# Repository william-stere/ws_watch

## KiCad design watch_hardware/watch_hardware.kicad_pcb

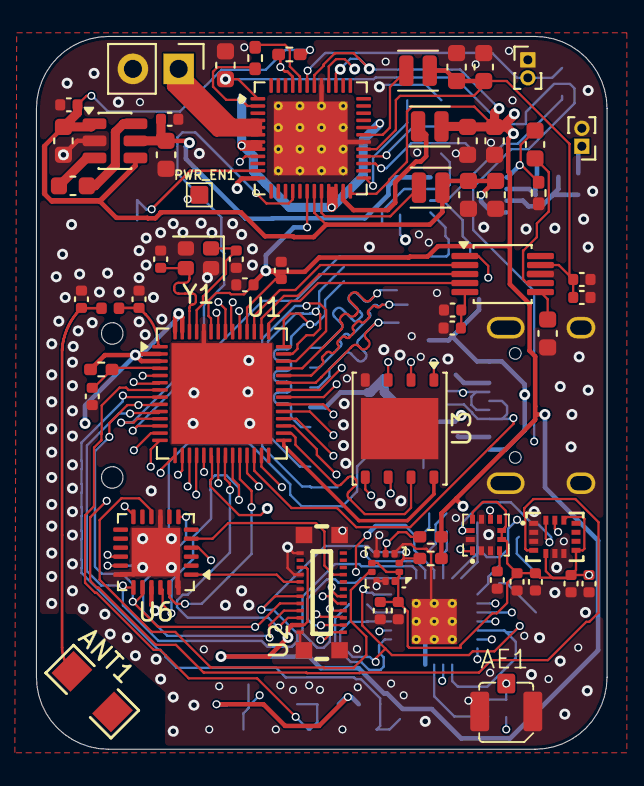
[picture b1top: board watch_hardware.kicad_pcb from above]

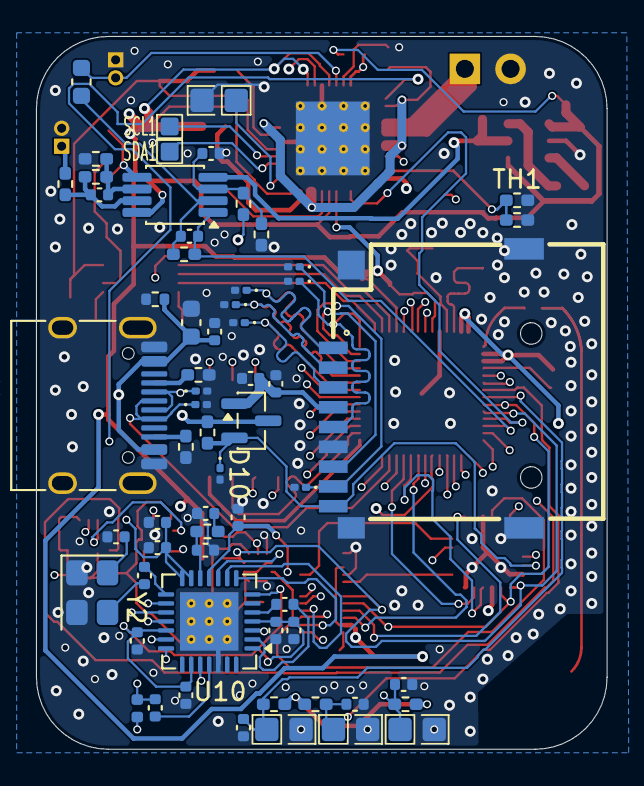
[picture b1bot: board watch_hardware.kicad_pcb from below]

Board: 4 copper layers, 31.7 x 39.6 mm, 121 parts (62 on the bottom side), 98 nets.

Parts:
AE1: IPEX_1
ANT1: ANT-SMD-2_L3.2-W1.6
BT1: Battery_Cell; PinHeader_1x02_P2.54mm_Vertical
C1, C2, C3, C6, C12, C13, C14, C17, C24, C25, C29, C30, C32, C37, C38, C40, C41, C44, C47, C48: 100nF; C_0402_1005Metric
C4, C11, C15, C16, C22, C26, C28: 10uF; C_0402_1005Metric
C5: 2.7pF; C_0402_1005Metric
C7: 1pF; C_0402_1005Metric
C8: 1uF; C_0402_1005Metric
C9, C10: 18pF; C_0402_1005Metric
C18, C20, C23, C43, C45, C46, C49, C50, C51, C52, C53, C54, C55, C56: 10uF; C_0603_1608Metric
C19: 4.7uF; C_0402_1005Metric
C21: 270pF; C_0402_1005Metric
C27: 100pF; C_0402_1005Metric
C31, C33, C39: 470pF; C_0402_1005Metric
C34, C35, C42: 10nF; C_0402_1005Metric
C36: 27pF; C_0402_1005Metric
D1: TVS; R_0402_1005Metric
D2, D3, D4, D5, D6, D7, D8, D9, D10: D_TVS; D_0201_0603Metric
J1: USB_C_Receptacle_USB2.0_16P; usb_C_16p
J2: TF_Card; TF-SMD_TF-PUSH
L1: 1.5nH; L_0402_1005Metric
L2: 47nH; L_0402_1005Metric
L3, L4, L5: 2.2uH; L_Changjiang_FTC201610S
LS1: Speaker; PinHeader_1x02_P1.00mm_Vertical
MK1: Microphone; PinHeader_1x02_P1.00mm_Vertical
PWR_EN1: TestPoint; testpoint
Q1: PMOS; SOT-23
R1, R2, R3, R6, R11, R16, R19, R20: 10k; R_0402_1005Metric_Pad0.72x0.64mm_HandSolder
R4, R5: 5.1k; R_0402_1005Metric_Pad0.72x0.64mm_HandSolder
R7, R8: 4.7k; R_0402_1005Metric_Pad0.72x0.64mm_HandSolder
R9: 100k; R_0402_1005Metric_Pad0.72x0.64mm_HandSolder
R10: 270k; R_0402_1005Metric_Pad0.72x0.64mm_HandSolder
R12: 8.2k; R_0402_1005Metric_Pad0.72x0.64mm_HandSolder
R13, R17: 20k; R_0402_1005Metric_Pad0.72x0.64mm_HandSolder
R14: 22k; R_0402_1005Metric_Pad0.72x0.64mm_HandSolder
R15: 50; R_0402_1005Metric_Pad0.72x0.64mm_HandSolder
R18: 75k; R_0402_1005Metric_Pad0.72x0.64mm_HandSolder
SCL1: TestPoint; testpoint
SDA1: TestPoint; testpoint
SW1, SW2, SW3, SW4: SW_Push; switch_base
TH1: 10k;B 3950K; R_0402_1005Metric_Pad0.72x0.64mm_HandSolder
U1: ESP32-S3; QFN-56-1EP_7x7mm_P0.4mm_EP5.6x5.6mm
U2: TK018F3716; CONN-SMD_BTB0.408-24PLBDR-M41
U3: W25Q128JVP; WSON-8-1EP_6x5mm_P1.27mm_EP3.4x4.3mm
U4: LIS3MDL; LGA-12_L2.0-W2.0-P0.50-BL
U5: LSM6DSOW; LGA-14L_L3.0-W2.5-P0.50-TL
U6: AW9523B; QFN-24-1EP_4x4mm_P0.5mm_EP2.7x2.7mm
U7: LPS22HB; ST_HLGA-10_2x2mm_P0.5mm_LayoutBorder3x2y
U8: CJC4344H; MSOP-10_3x3mm_P0.5mm
U9: OPA2192; VSSOP-8_3x3mm_P0.65mm
U10: MAX2769C; QFN-28-1EP_5x5mm_P0.5mm_EP3.25x3.25mm_ThermalVias
U11: LM2664; SOT-23-6
U12: TPS652170; VQFN-48-1EP_6x6mm_P0.4mm_EP4.1x4.1mm_ThermalVias
Y1: Crystal_GND24; Crystal_SMD_2016-4Pin_2.0x1.6mm
Y2: 7Q16300001; Crystal_SMD_3225-4Pin_3.2x2.5mm

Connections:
+2V0: C18.1, MK1.2 (+), R10.1, U12.43 (LS2_OUT)
+3.3V: C43.1, C44.2, C51.2, C52.2, L3.1, R19.2, U9.8 (V+), U11.1 (V+), U11.4 (SD), U12.19 (VDCDC1)
+3.3VADC: C30.2, C32.2, C37.2, C38.2, C40.2, C41.1, C42.1, C50.1, U10.4 (Vcc_rf), U10.7 (SHDN), U10.11 (Vcc_vco), U10.13 (Vcc_cp), U10.14 (Vccd), U10.19 (Vcc_adc), U10.23 (Vcc_if), U12.1 (VLDO2)
+3.3VDAC: C25.1, C26.1, C55.2, C56.2, L5.2, U8.9 (VA), U12.29 (VDCDC3)
+3.3VP: C11.1, C12.1, C14.1, C15.1, C22.1, C24.1, U4.5 (Vdd), U4.6 (Vdd_IO), U4.10 (CS), U5.5 (VDDIO), U5.8 (VDD), U5.12 (CS), U7.1 (Vdd_IO), U7.6 (~CS), U7.10 (VDD), U12.40 (LS1_OUT)
+3V3: C4.1, C6.1, C53.1, C54.1, L4.1, Q1.3 (S), R1.2, R2.2, R3.2, R6.1, R7.1, R8.1, R16.2, U1.2 (VDD3P3), U1.3 (VDD3P3), U1.20 (VDD3P3_RTC), U1.46 (VDD3P3_CPU), U1.51 (GPIO45), U1.55 (VDDA), U1.56 (VDDA), U2.15, U2.23, U6.21 (VCC), U12.18 (VIO), U12.24 (VDCDC2), U12.39 (LS1_IN), U12.42 (LS2_IN)
+5V: C47.2, C49.2, D1.1 (A1), J1.A4 (VBUS), J1.A9 (VBUS), J1.B4 (VBUS), J1.B9 (VBUS), U12.12 (USB)
-3V3: C45.2, C48.1, U9.4 (V-), U11.5 (OUT)
/+IN_A: C19.2, R9.1, R10.2, U9.3 (+IN_A)
/-IN_A: C18.2, C21.1, R11.1, U9.2 (-IN_A)
/ADC_CLK: U1.49 (U0TXD), U10.16 (CLKOUT)
/AOUTL: C23.2, R12.2, U9.5 (+IN_B)
/AW_INT: U1.23 (GPIO17), U6.22 (~INT)
/AW_RST: U1.24 (GPIO18), U6.23 (~RST)
/CS#: U1.32 (SPICS0/GPIO29), U3.1 (~CS)
/DI: U1.35 (SPID/GPIO32), U3.5 (DI/IO_{0})
/DO: U1.34 (SPIQ/GPIO31), U3.2 (DO/IO_{1})
/GPIO0: C1.1, R1.1, SW1.1, U1.5 (GPIO0)
/GPIO2: C2.1, R2.1, SW2.1, U1.7 (GPIO2)
/GPIO3: C3.1, R3.1, SW3.1, U1.8 (GPIO3)
/HOLD#: U1.30 (SPIHD/GPIO27), U3.7 (~HOLD/~RESET/IO_{3})
/I2s_BCK: U1.45 (MTDO/JTAG/GPIO40), U8.2 (SCLK)
/I2s_MCLK: U1.43 (GPIO38), U8.4 (MCLK)
/I2s_SD: U1.47 (MTDI/JTAG/GPIO41), U8.1 (SDIN)
/I2s_WS: U1.44 (MTCK/JTAG/GPIO39), U8.3 (LRCK)
/LEDA: U2.17, U6.1 (P1_0)
/LIS_DRDY: U4.8 (DRDY), U6.4 (P1_3)
/LPS_INT: U6.10 (P0_4), U7.7 (INT_DRDY)
/LSM_INT: U5.4 (INT1), U6.12 (P0_6)
/L_CS: U1.15 (GPIO10), U2.1
/L_D1: U1.17 (GPIO12), U2.3
/L_D2: U1.21 (GPIO15/ADC2_CH4/XTAL_32K_P), U2.6
/L_D3: U1.19 (GPIO14), U2.5
/L_INT: U1.22 (GPIO16/ADC2_CH5/XTAL_32K_N), U2.22
/L_MOSI: U1.16 (GPIO11), U2.2, U10.8 (SDATA)
/L_RST: U2.9, U6.5 (P0_0)
/L_SCK: U1.18 (GPIO13), U2.4, U10.9 (SCLK)
/MAX_CS: U1.50 (U0RXD), U10.10 (CS)
/MAX_I0: U1.27 (GPIO21), U10.20 (I0)
/MAX_I1: U1.14 (GPIO9), U10.21 (I1)
/MAX_IDLE: U6.16 (P1_6), U10.24 (IDLE)
/MAX_Q0: U1.36 (SPICLK_N/GPIO48), U10.18 (Q0)
/MAX_Q1: U1.48 (MTMS/JTAG/GPIO42), U10.17 (Q1)
/MIC_IN: C21.2, R11.2, U1.12 (GPIO7), U9.1 (OUT_A)
/MUX_OUT: U1.11 (GPIO6), U12.16 (MUX_OUT)
/PMIC_INT: R19.1, U1.6 (GPIO1), U12.45 (nINT)
/PWR_EN: PWR_EN1.1 (1_1), U1.13 (GPIO8), U12.9 (PWR_EN)
/SCK: U1.33 (SPICLK/GPIO30), U3.6 (CLK)
/SCL0: R8.2, SCL1.1 (1_1), U1.10 (GPIO5), U2.19, U4.1 (SCL/SPC), U5.13 (SCL), U6.19 (SCL), U7.2 (SCL), U12.28 (SCL)
/SDA0: R7.2, SDA1.1 (1_1), U1.9 (GPIO4), U2.20, U4.11 (SDA/SDI/SDO), U5.14 (SDA), U6.20 (SDA), U7.4 (SDA), U12.27 (SDA)
/SYS: R20.2, U12.2 (VINLDO), U12.7 (SYS), U12.8 (SYS), U12.21 (VIN_DCDC1), U12.22 (VIN_DCDC2), U12.32 (VIN_DCDC3)
/TF_CD: D10.1 (A1), J2.CD, Q1.2 (G), R16.1, U6.17 (P1_7)
/TF_CLK: D7.1 (A1), J2.5 (CLK), U1.42 (GPIO37)
/TF_CMD: D6.1 (A1), J2.3 (CMD), U1.37 (SPICLK_P/GPIO47)
/TF_DAT0: D8.1 (A1), J2.7 (DAT0), U1.41 (GPIO36)
/TF_DAT1: D9.1 (A1), J2.8 (DAT1), U1.40 (GPIO35)
/TF_DAT2: D4.1 (A1), J2.1 (DAT2), U1.39 (GPIO34)
/TF_DAT3: D5.1 (A1), J2.2 (DAT3/CD), U1.38 (GPIO33)
/TF_VDD: C28.1, C29.1, J2.4 (VDD), Q1.1 (D)
/T_RST: U2.21, U6.7 (P0_2)
/USB_D+: D3.1 (A1), J1.A6 (D+), J1.B6 (D+), U1.26 (GPIO20)
/USB_D-: D2.1 (A1), J1.A7 (D-), J1.B7 (D-), U1.25 (GPIO19)
/VDD_SPI: U1.29 (VDD_SPI), U3.8 (VCC)
/WP#: U1.31 (SPIWP/GPIO28), U3.3 (~WP/IO_{2})
GND: AE1.2 (Shield), BT1.2 (-), C1.2, C2.2, C3.2, C4.2, C5.2, C6.2, C7.2, C8.1, C9.1, C10.2, C11.2, C12.2, C13.2, C14.2, C15.2, C16.1, C17.1, C19.1, C20.1, C22.2, C24.2, C25.2, C26.2, C28.2, C29.2, C30.1, C32.1, C35.1, C36.2, C37.1, C38.1, C39.2, C40.1, C41.2, C42.2, C43.2, C44.1, C45.1, C47.1, C48.2, C49.1, C50.2, C51.1, C52.1, C53.2, C54.2, C55.1, C56.1, D1.2 (A2), D2.2 (A2), D3.2 (A2), D4.2 (A2), D5.2 (A2), D6.2 (A2), D7.2 (A2), D8.2 (A2), D9.2 (A2), D10.2 (A2), J1.A1 (GND), J1.A12 (GND), J1.B1 (GND), J1.B12 (GND), J1.SH (SHIELD), J2.6 (VSS), J2.SH (SHIELD), LS1.2, MK1.1 (-), R4.2, R5.2, R9.2, R12.1, R13.1, R18.2, SW1.2, SW2.2, SW3.2, SW4.2, TH1.2, U1.52 (GPIO46), U1.57 (GND), U2.13, U2.16, U2.18, U2.24, U2.25, U2.26, U2.27, U2.28, U3.4 (GND), U3.9 (EP), U4.2 (Res), U4.3 (GND), U4.9 (SD0/SA1), U4.12 (Res), U5.1 (SDO/SA0), U5.2 (SDx), U5.3 (SCx), U5.6 (GND), U5.7 (GND), U6.9 (GND), U6.18 (AD0), U6.24 (AD1), U6.25 (GND), U7.3 (GND), U7.5 (SA0), U7.8 (GND), U7.9 (GND), U8.8 (GND), U10.26 (PGM), U10.29 (EP), U11.2 (GND), U12.30 (PGND), U12.41 (AGND), U12.49 (TP), Y1.2 (G), Y1.4 (G), Y2.1 (GND/NC), Y2.2 (GND)
unnamed: AE1.1 (A), C31.2, L2.2
unnamed: ANT1.1 (INPUT_1), C5.1, L1.1
unnamed: BT1.1 (+), U12.4 (BAT), U12.5 (BAT), U12.6 (BAT_SENSE)
unnamed: C39.1, R17.1
unnamed: J1.A5 (CC1), R4.1
unnamed: J1.B5 (CC2), R5.1
unnamed: LS1.1, R15.1
unnamed: C8.2, R6.2, U1.4 (CHIP_PU)
unnamed: C7.1, L1.2, U1.1 (LNA_IN)
unnamed: C10.1, U1.53 (XTAL_N), Y1.1
unnamed: C9.2, U1.54 (XTAL_P), Y1.3
unnamed: C13.1, U4.4 (C1)
unnamed: C23.1, U8.7 (AOUTL)
unnamed: C20.2, U8.6 (FILT+)
unnamed: C16.2, C17.2, U8.5 (VQ)
unnamed: C27.2, R13.2, R14.1, U9.6 (-IN_B)
unnamed: C27.1, R14.2, R15.2, U9.7 (OUT_B)
unnamed: L2.1, U10.3 (ANTBIAS)
unnamed: C36.1, R17.2, U10.12 (CPOUT)
unnamed: C31.1, U10.25 (LNA2)
unnamed: C33.2, U10.2 (LNAOUT)
unnamed: C33.1, U10.5 (MIXIN)
unnamed: C34.2, U10.15 (XTAL)
unnamed: C46.1, U11.6 (CAP+)
unnamed: C46.2, U11.3 (CAP-)
unnamed: L3.2, U12.20 (L1)
unnamed: L4.2, U12.23 (L2)
unnamed: L5.1, U12.31 (L3)
unnamed: SW4.1, U12.25 (PB_IN)
unnamed: R18.1, TH1.1, U12.11 (TS)
unnamed: R20.1, U12.44 (nRESET)
unnamed: C34.1, Y2.3 (OUTPUT)
unnamed: C35.2, Y2.4 (VCC)

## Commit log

2025-12-27 创建项目并，编写了Kconfig
2026-01-10 日常提交
2026-01-11 清除了原来bl
2026-02-14 不使用自定义二级bootloader，添加未完成的驱动，添加依赖，显示驱动已测试
2026-02-15 modified: components/cst816d/cst816d.c modified: components/cst816d/include/cst816d.h modified: main/ws_watch.c
2026-02-20 modified: .gitignore modified: components/esp_lcd_nv3030b/esp_lcd_nv3030b.c modified: components/esp_lcd_nv3030b/include/esp_lcd_nv3030b.h modified: main/ws_watch.c modified: sdkconfig modified: sdkc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
2026-02-24 添加docs
2026-03-29 基本重新设计了硬件部分
2026-04-04 修改了电路部分，使用外部flash
2026-04-11 添加了一个符号
2026-04-11 添加图页，大幅修改电源轨
2026-04-12 继续修改
2026-04-17 电源轨修改
2026-04-18 原理图应该完成了吧……
2026-04-18 简单的画了了一下PCB
2026-04-19 简单天线匹配
2026-04-19 daily
2026-04-25 更换PMIC，使用TPS65217A减小面积与降低成本
2026-04-25 添加文档
2026-05-01 准备添加卫星定位
2026-05-02 完成电路设计
2026-05-02 修改电路设计，未完成，还需修改，以符合生产需求
2026-05-03 修改完电路
2026-05-03 修改了电路，以符合生产需求
2026-05-03 孔径修改为0.3mm
2026-05-30 修改了电路
